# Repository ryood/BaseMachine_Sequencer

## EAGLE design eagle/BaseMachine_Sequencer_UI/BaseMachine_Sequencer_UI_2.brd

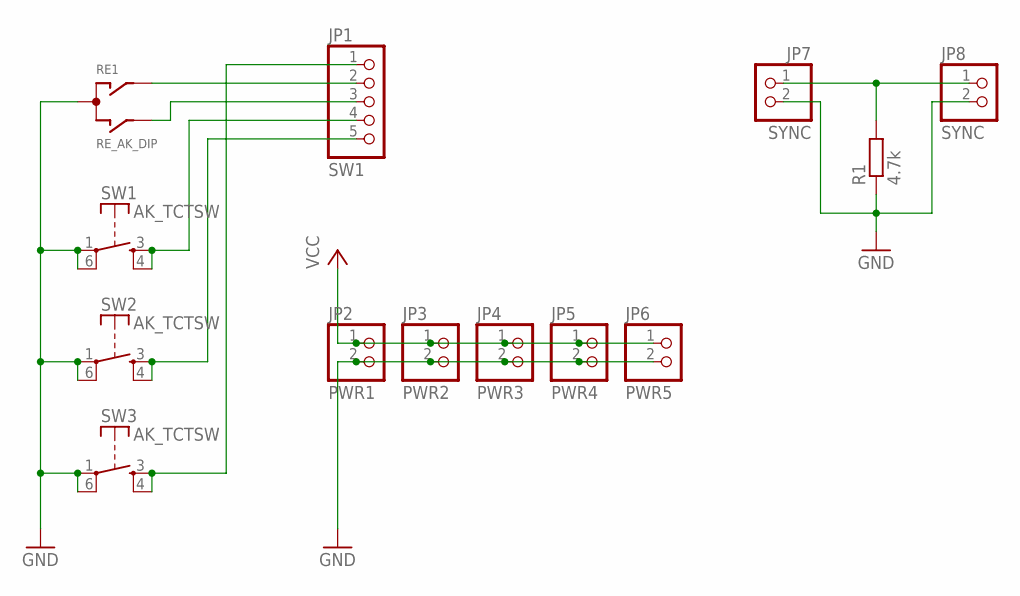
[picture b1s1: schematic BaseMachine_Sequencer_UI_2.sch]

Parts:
JP1: SW1; 1X05/90
JP2: PWR1; 1X02/90
JP3: PWR2; 1X02
JP4: PWR3; 1X02
JP5: PWR4; 1X02
JP6: PWR5; 1X02
JP7: SYNC; 1X02/90
JP8: SYNC; 1X02
R1: 4.7k; 0207/7
RE1: RE_AK_DIP
SW1, SW2, SW3: AK_TCTSW; TME1

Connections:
GND: JP2.2, JP3.2, JP4.2, JP5.2, JP6.2, JP7.2, JP8.2, R1.1, RE1.P$3 (C), SW1.1, SW1.6, SW2.1, SW2.6, SW3.1, SW3.6
unnamed: JP1.2, RE1.P$2 (A)
unnamed: JP1.5, SW2.3 (S), SW2.4 (S)
unnamed: JP1.3, RE1.P$4 (B)
unnamed: JP1.4, SW1.3 (S), SW1.4 (S)
unnamed: JP7.1, JP8.1, R1.2
unnamed: JP1.1, SW3.3 (S), SW3.4 (S)
VCC: JP2.1, JP3.1, JP4.1, JP5.1, JP6.1

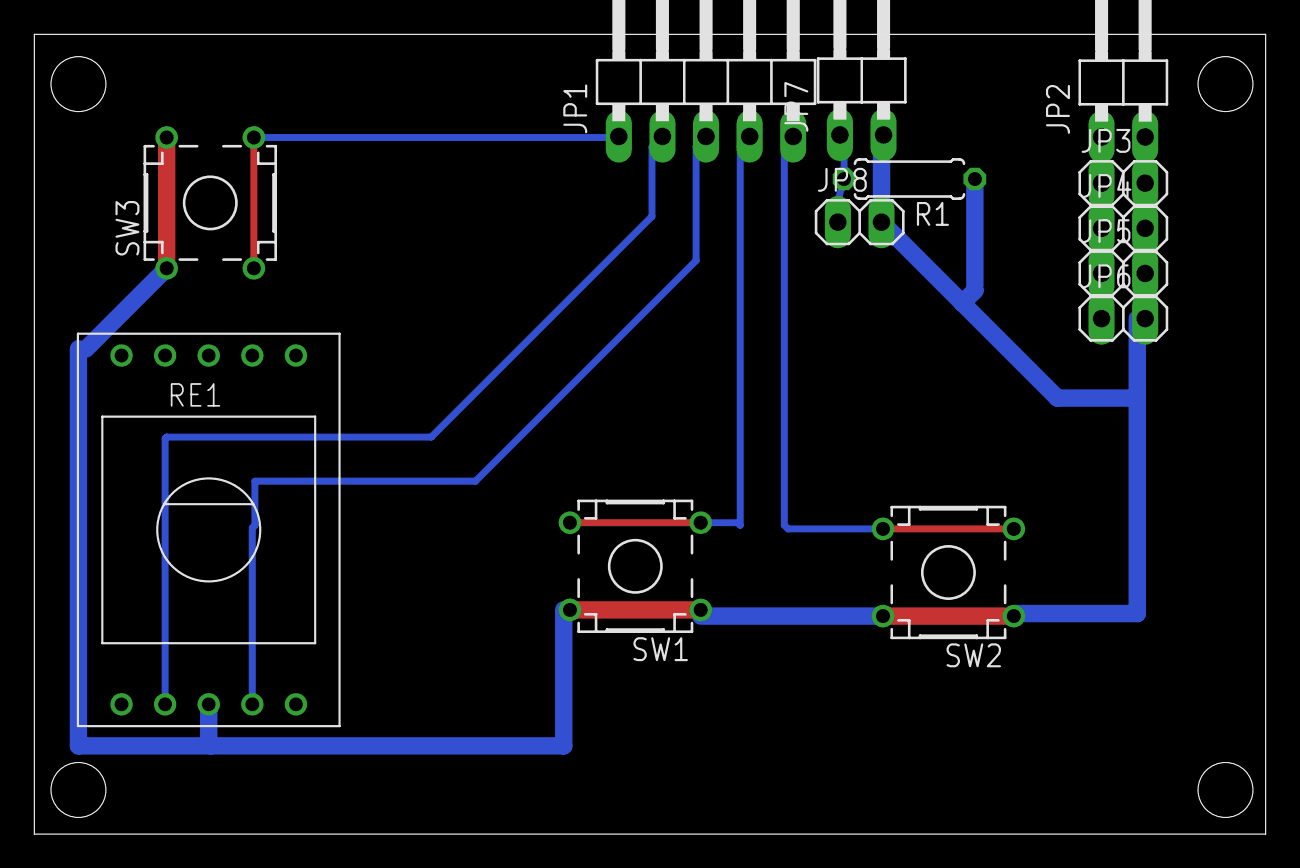
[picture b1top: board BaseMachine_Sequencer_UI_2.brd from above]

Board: 2 copper layers, 71.7 x 46.6 mm, 13 parts (0 on the bottom side), 8 nets.

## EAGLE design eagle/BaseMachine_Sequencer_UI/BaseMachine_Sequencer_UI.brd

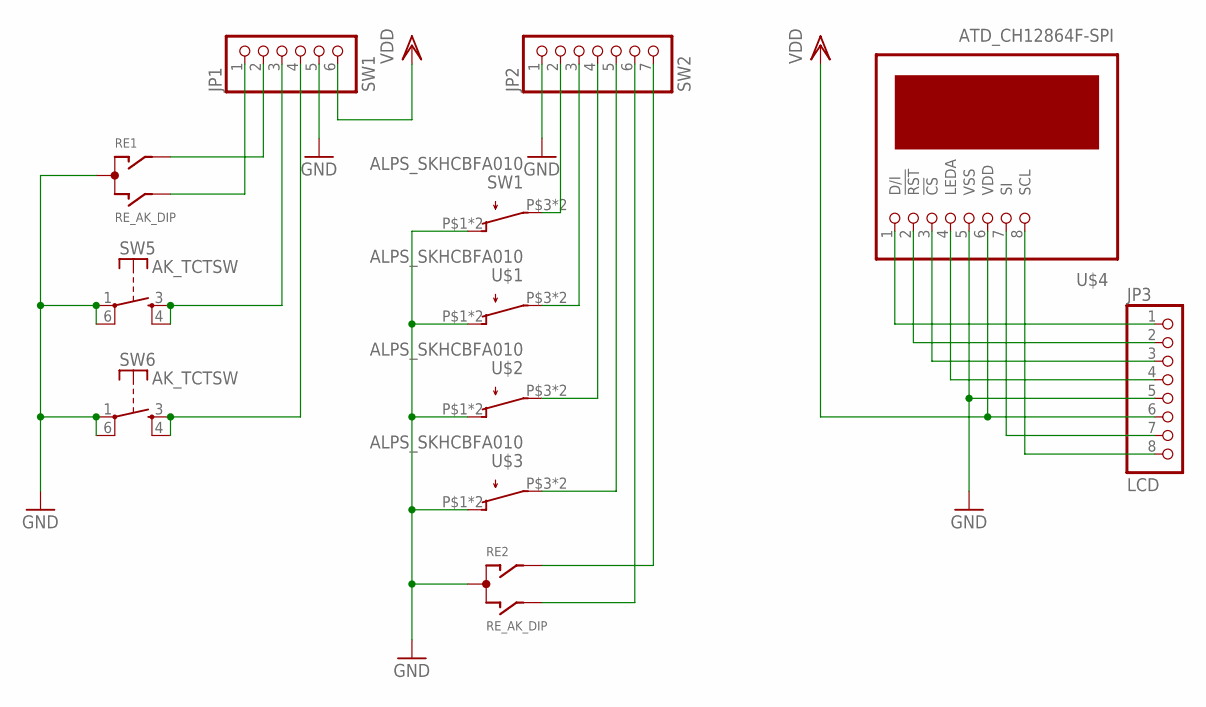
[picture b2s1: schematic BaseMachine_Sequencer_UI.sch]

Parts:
JP1: SW1; 1X06/90
JP2: SW2; 1X07/90
JP3: LCD; 1X08/90
RE1, RE2: RE_AK_DIP
SW1: ALPS_SKHCBFA010
SW5, SW6: AK_TCTSW; TME1
U$1, U$2, U$3: ALPS_SKHCBFA010
U$4: ATD_CH12864F-SPI; ATD-CH12864F-SPI

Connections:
GND: JP1.5, JP2.1, JP3.5, RE1.P$3 (C), RE2.P$3 (C), SW1.P$1 (O), SW1.P$2 (O), SW5.1, SW5.6, SW6.1, SW6.6, U$1.P$1 (O), U$1.P$2 (O), U$2.P$1 (O), U$2.P$2 (O), U$3.P$1 (O), U$3.P$2 (O), U$4.5 (VSS)
LCD1: JP3.1, U$4.1 (D/I)
unnamed: JP2.4, U$2.P$3, U$2.P$4
unnamed: JP2.7, RE2.P$2 (A)
unnamed: JP2.2, SW1.P$3, SW1.P$4
unnamed: JP3.3, U$4.3 (!CS)
unnamed: JP2.3, U$1.P$3, U$1.P$4
unnamed: JP2.6, RE2.P$4 (B)
unnamed: JP2.5, U$3.P$3, U$3.P$4
unnamed: JP3.4, U$4.4 (LEDA)
unnamed: JP1.1, RE1.P$4 (B)
unnamed: JP1.3, SW5.3 (S), SW5.4 (S)
unnamed: JP1.2, RE1.P$2 (A)
unnamed: JP3.2, U$4.2 (!RST)
unnamed: JP1.4, SW6.3 (S), SW6.4 (S)
unnamed: JP3.7, U$4.7 (SI)
unnamed: JP3.8, U$4.8 (SCL)
VDD: JP1.6, JP3.6, U$4.6 (VDD)

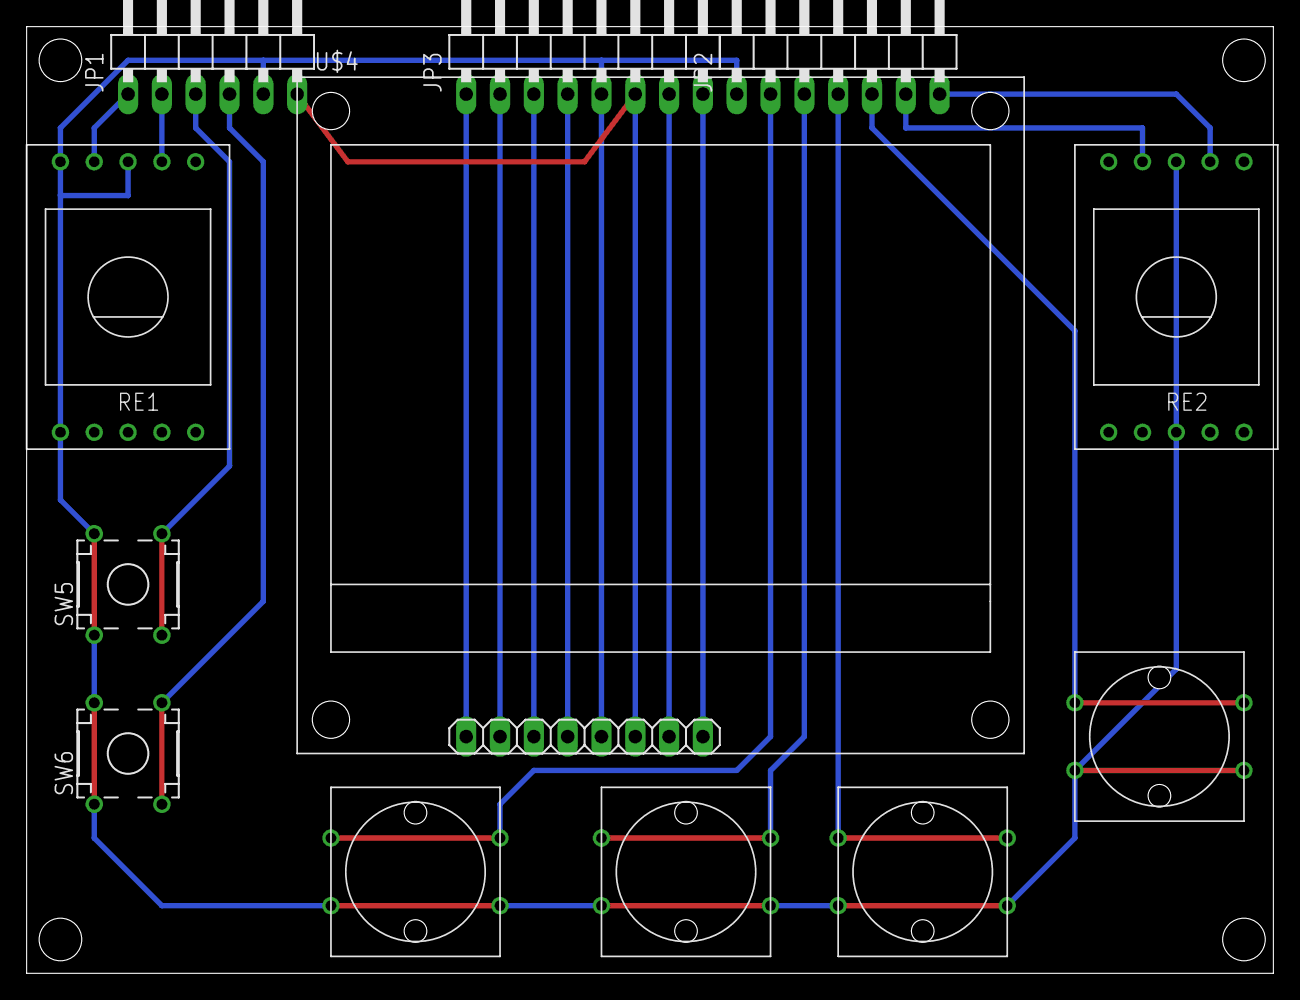
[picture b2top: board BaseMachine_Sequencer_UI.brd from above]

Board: 2 copper layers, 93.7 x 71.1 mm, 12 parts (0 on the bottom side), 18 nets.

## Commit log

2016-08-17 Add: UI Test (Tact SW, Rotary Encoder, POT)
2016-08-20 Bugfix: Power Line
2016-09-01 Add: Board design
2016-09-01 Update parts position
2016-09-01 routing
2016-09-04 Update: UI & UI2 Board Design
2016-09-04 Update: ベースマシンUI一覧表.xlsx
2016-09-09 Add: Documents
2016-12-19 Clean up
2017-05-13 Add: Nucleo firmware's binaries
2017-08-23 Add: PNG of the schematics and the boards
